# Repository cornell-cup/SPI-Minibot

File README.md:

# SPI-Minibot
For SPI communication between Pi and Arduino (should support up to 4 devices) with new PCB design

HOW TO RUN:
You type into terminal
1. cd SPI-Minibot
2. python -c 'import SPI_test; SPI_test.claw()'

NOTE: change .claw() function to whatever function you want to run
(ex. shoulder(), left(),right(),fwd(),back(),armL() [stepper], armR()[also stepper]

SPI_1.ino refers to top arduino (Closest to the raspberry pi)
SPI_A2.ino referes to bottom arduino (closest to battery)

When loading Arduino (.ino) programs:
Connect USB to serial (USB to jumper cables) and run SPI_1.ino on the top arduino
and then connect the cable to the bottom arduino and run SPI_A2.ino on the bottom one. 

When cloning this Repo (If not already loaded on the Pi):
1. Make sure you have SPI enabled (easiest way is through the GUI in NOOBS so you can just go to configuration and enable)
      Otherwise on terminal do ifconfig and select the option for serial (I think option 6, will verify later)
2. Make sure you have SCL,SDA,CE0, and CE1 wires all connected

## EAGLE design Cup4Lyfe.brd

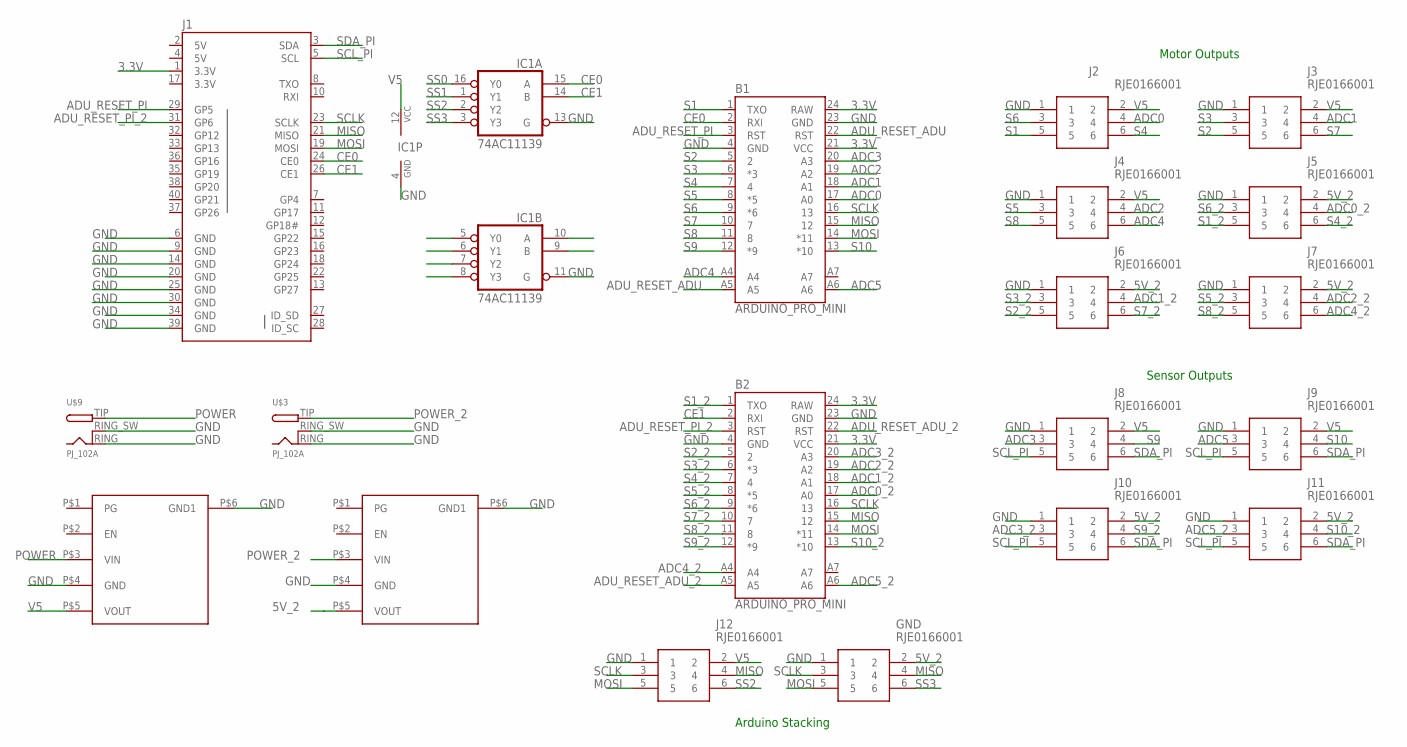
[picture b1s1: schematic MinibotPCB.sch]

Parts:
B1, B2: ARDUINO_PRO_MINI
GND: RJE0166001; RJE0166001_1
IC1: 74AC11139; DIL16
J1: RASPBERRYPI-40-PIN-GPIO_PTH_NO_SHROUD; 2X20
J2, J3, J4, J5, J6, J7, J8, J9, J10, J11, J12: RJE0166001; RJE0166001_1
U$1, U$2: D24V22F5
U$3, U$9: PJ_102A; PJ-102A

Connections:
3.3V: B1.21 (VCC), B1.24 (RAW), B2.21 (VCC), B2.24 (RAW), J1.1 (3.3V), J1.17 (3.3V)
5V: J1.2 (5V), J1.4 (5V)
5V_2: GND.2, J5.2, J6.2, J7.2, J10.2, J11.2, U$1.P$5 (VOUT)
ADC0: B1.17 (A0), J2.4
ADC0_2: B2.17 (A0), J5.4
ADC1: B1.18 (A1), J3.4
ADC1_2: B2.18 (A1), J6.4
ADC2: B1.19 (A2), J4.4
ADC2_2: B2.19 (A2), J7.4
ADC3: B1.20 (A3), J8.3
ADC3_2: B2.20 (A3), J10.3
ADC4: B1.A4, J4.6
ADC4_2: B2.A4, J7.6
ADC5: B1.A6, J9.3
ADC5_2: B2.A6, J11.3
ADU_RESET_ADU: B1.22 (RST), B1.A5
ADU_RESET_ADU_2: B2.22 (RST), B2.A5
ADU_RESET_PI: B1.3 (RST), J1.29 (GP5)
ADU_RESET_PI_2: B2.3 (RST), J1.31 (GP6)
CE0: B1.2 (RXI), IC1.15 (A), J1.24 (CE0)
CE1: B2.2 (RXI), IC1.14 (B), J1.26 (CE1)
GND: B1.4 (GND), B1.23 (GND), B2.4 (GND), B2.23 (GND), GND.1, IC1.4 (GND), IC1.11 (G), IC1.13 (G), J1.6 (GND), J1.9 (GND), J1.14 (GND), J1.20 (GND), J1.25 (GND), J1.30 (GND), J1.34 (GND), J1.39 (GND), J2.1, J3.1, J4.1, J5.1, J6.1, J7.1, J8.1, J9.1, J10.1, J11.1, J12.1, U$1.P$4 (GND), U$1.P$6 (GND1), U$2.P$4 (GND), U$2.P$6 (GND1), U$3.RING (GND), U$3.RING_SW (GNDBREAK), U$9.RING (GND), U$9.RING_SW (GNDBREAK)
MISO: B1.15 (12), B2.15 (12), GND.4, J1.21 (MISO), J12.4
MOSI: B1.14 (*11), B2.14 (*11), GND.5, J1.19 (MOSI), J12.5
POWER: U$2.P$3 (VIN), U$9.TIP (PWR)
POWER_2: U$1.P$3 (VIN), U$3.TIP (PWR)
S1: B1.1 (TXO), J2.5
S1_2: B2.1 (TXO), J5.5
S2: B1.5 (2), J3.5
S2_2: B2.5 (2), J6.5
S3: B1.6 (*3), J3.3
S3_2: B2.6 (*3), J6.3
S4: B1.7 (4), J2.6
S4_2: B2.7 (4), J5.6
S5: B1.8 (*5), J4.3
S5_2: B2.8 (*5), J7.3
S6: B1.9 (*6), J2.3
S6_2: B2.9 (*6), J5.3
S7: B1.10 (7), J3.6
S7_2: B2.10 (7), J6.6
S8: B1.11 (8), J4.5
S8_2: B2.11 (8), J7.5
S9: B1.12 (*9), J8.4
S9_2: B2.12 (*9), J10.4
S10: B1.13 (*10), J9.4
S10_2: B2.13 (*10), J11.4
SCLK: B1.16 (13), B2.16 (13), GND.3, J1.23 (SCLK), J12.3
SCL_PI: J1.5 (SCL), J8.5, J9.5, J10.5, J11.5
SDA_PI: J1.3 (SDA), J8.6, J9.6, J10.6, J11.6
SS0: IC1.16 (Y0)
SS1: IC1.1 (Y1)
SS2: IC1.2 (Y2), J12.6
SS3: GND.6, IC1.3 (Y3)
V5: IC1.12 (VCC), J2.2, J3.2, J4.2, J8.2, J9.2, J12.2, U$2.P$5 (VOUT)

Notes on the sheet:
Arduino Stacking
Sensor Outputs
Motor Outputs

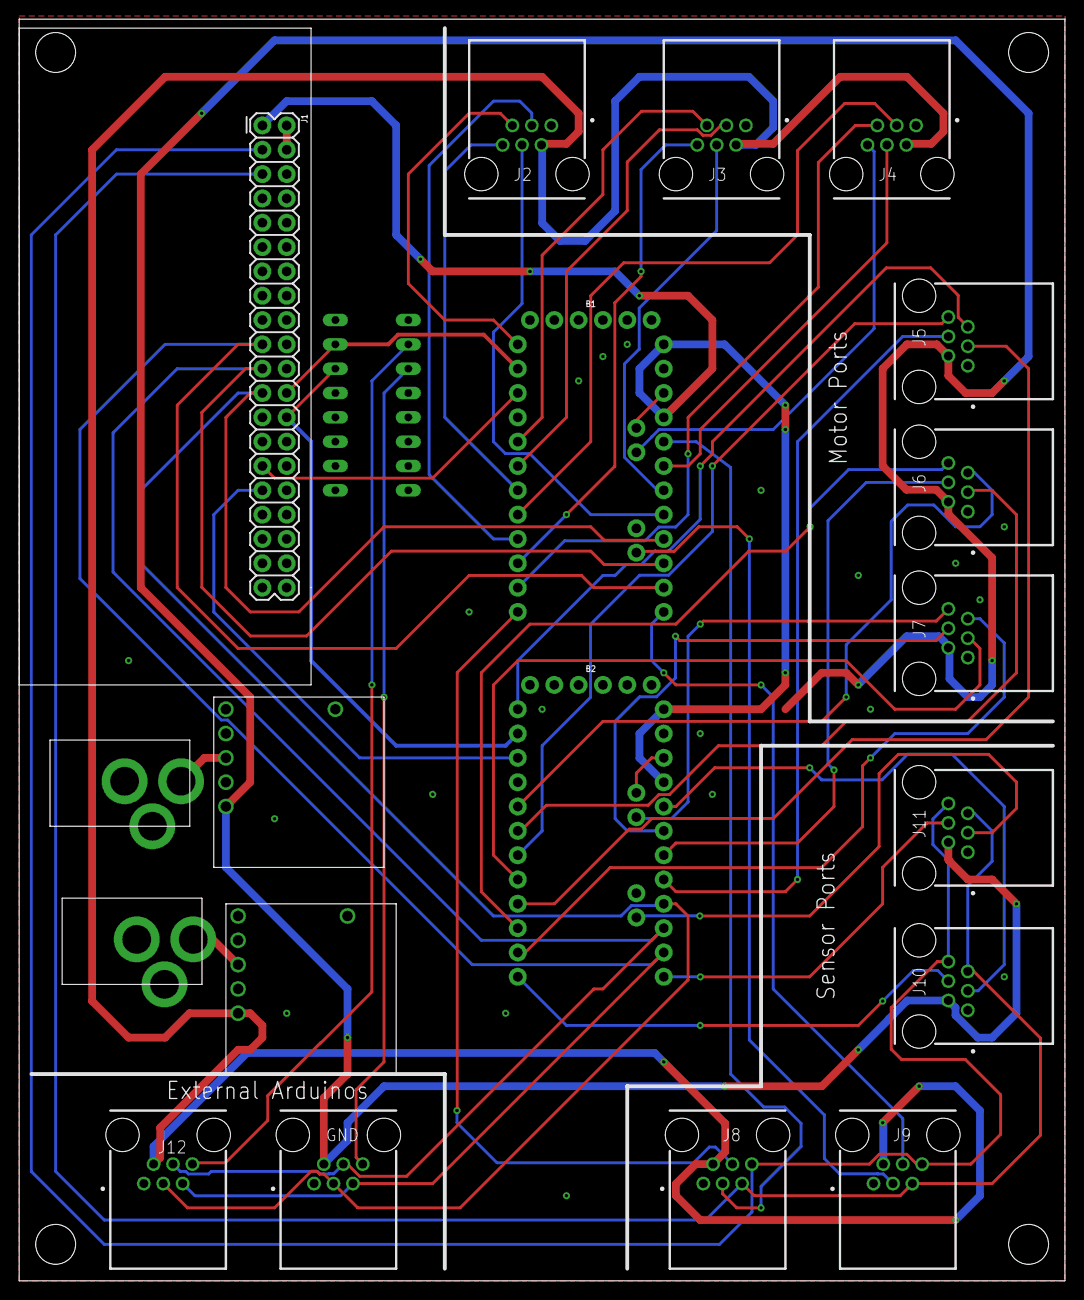
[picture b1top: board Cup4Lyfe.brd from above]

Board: 2 copper layers, 109.2 x 131.8 mm, 20 parts (1 on the bottom side), 52 nets.

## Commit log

2019-04-27 Added test file for SPI
2019-04-28 SPI working format wrong
2019-04-28 SPI working
2019-04-28 fixing
2019-04-29 python time
2019-04-29 Added functions
2019-04-29 fixed bugs
2019-04-29 Use for top arduino
2019-04-29 Use for arduino 2 (bottom)
2019-05-19 Added PCB files to show schematics
2019-05-19 Rename Cup4Lyfe.brd to MinibotPCB.brd
2019-05-19 Rename Cup4Lyfe.sch to MinibotPCB.sch
